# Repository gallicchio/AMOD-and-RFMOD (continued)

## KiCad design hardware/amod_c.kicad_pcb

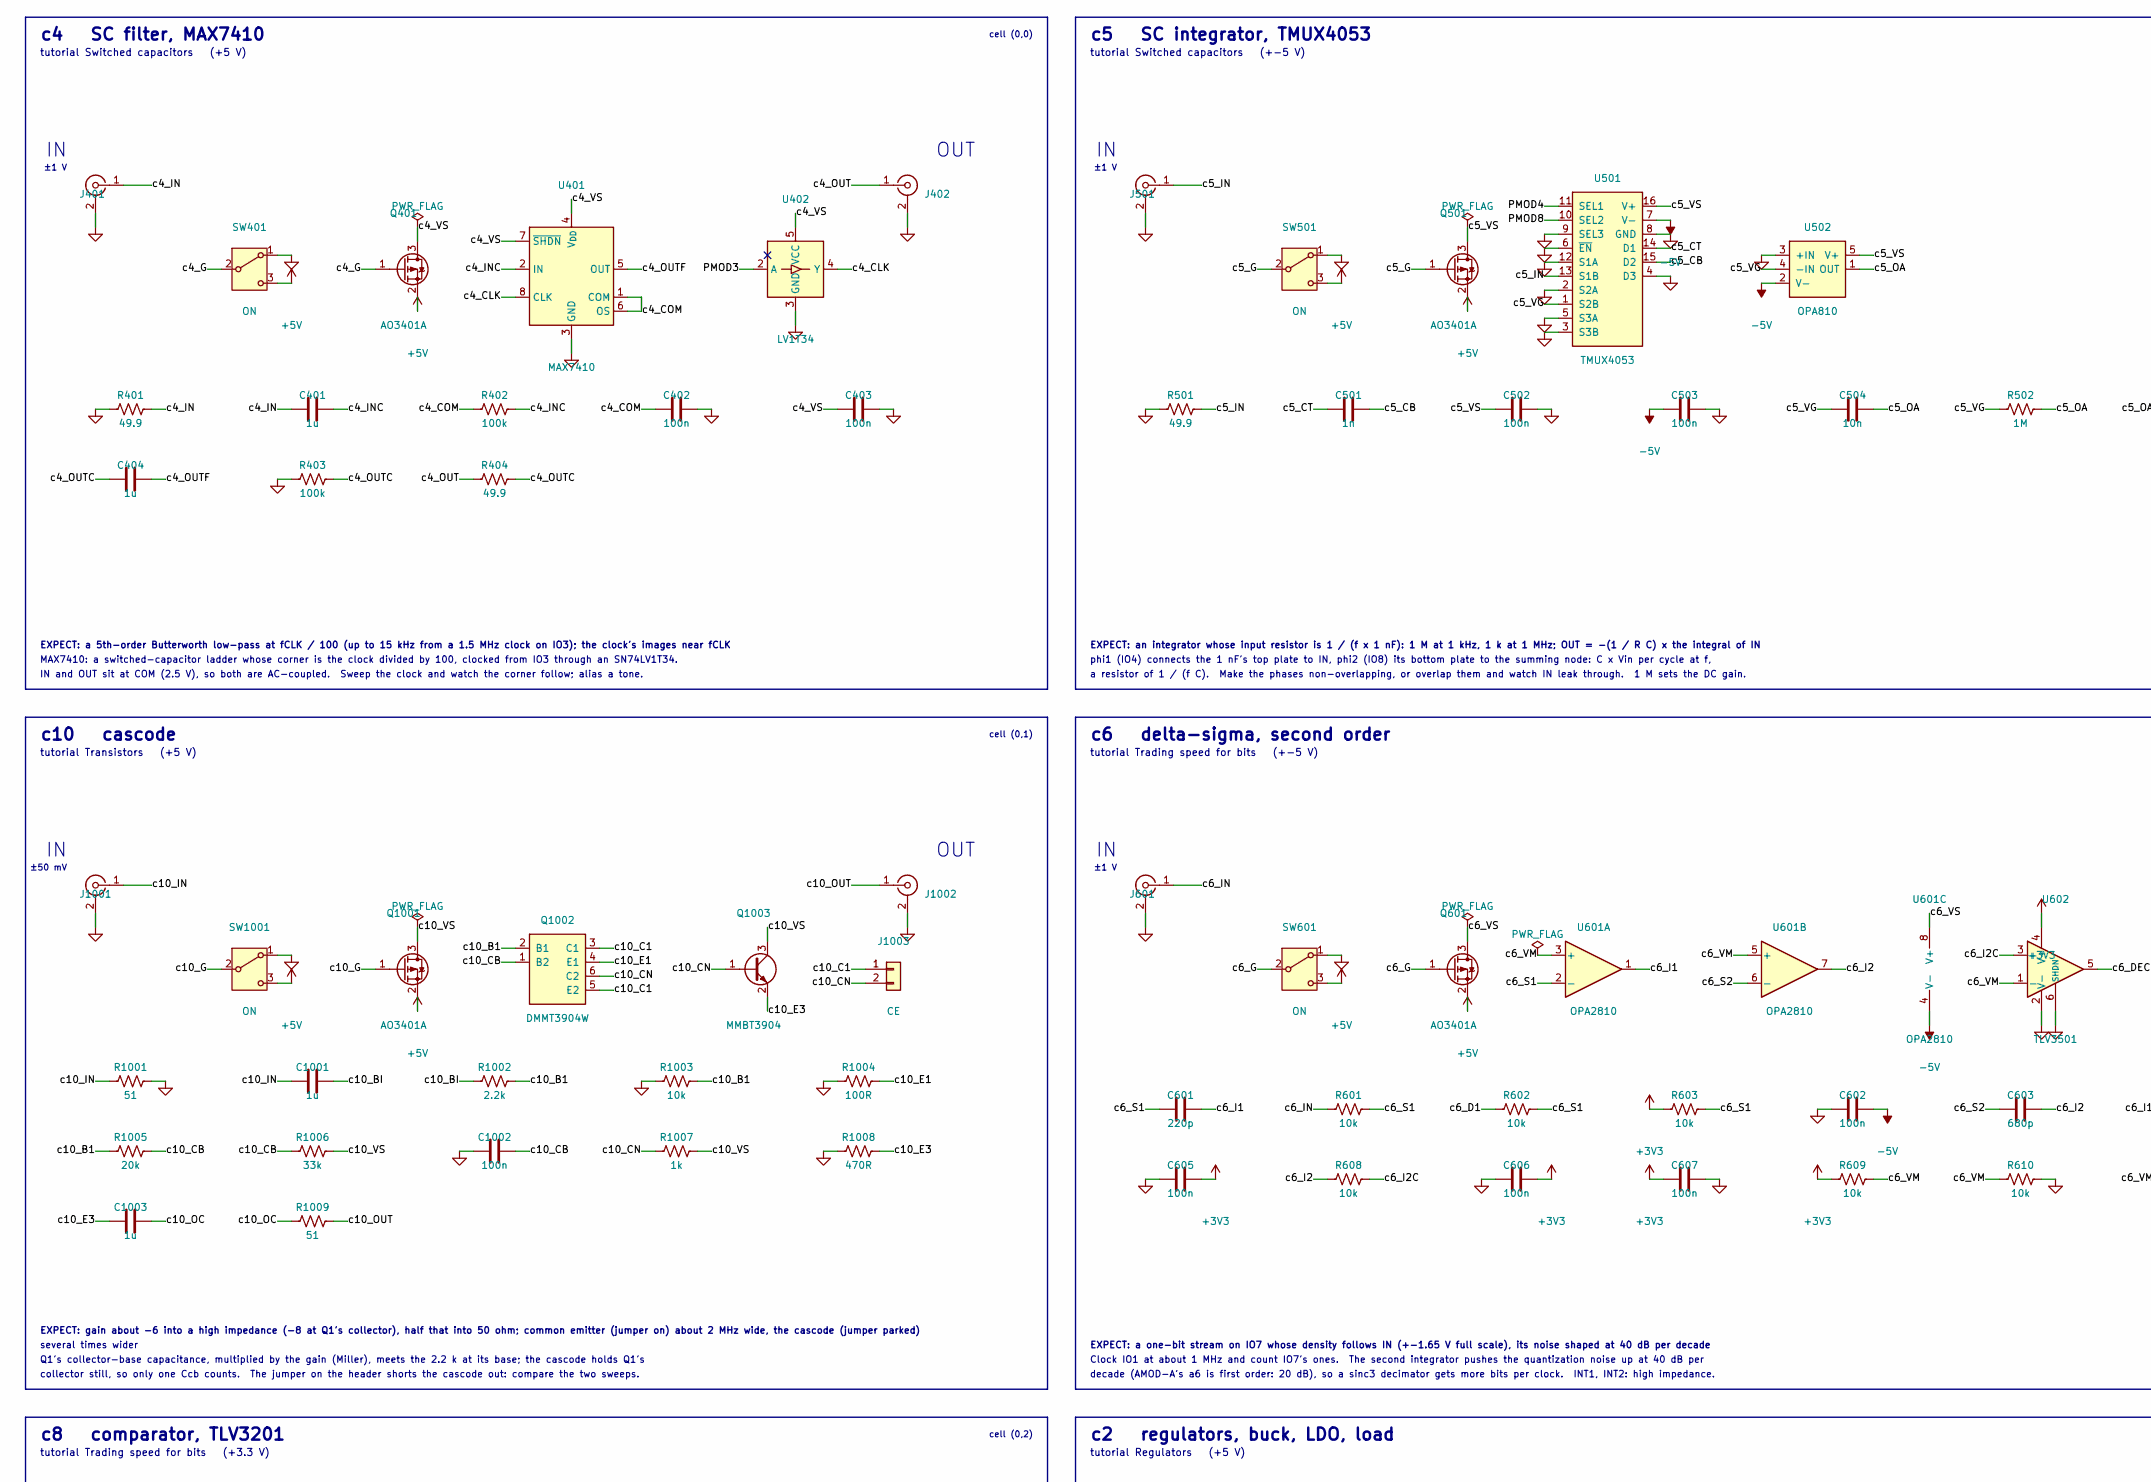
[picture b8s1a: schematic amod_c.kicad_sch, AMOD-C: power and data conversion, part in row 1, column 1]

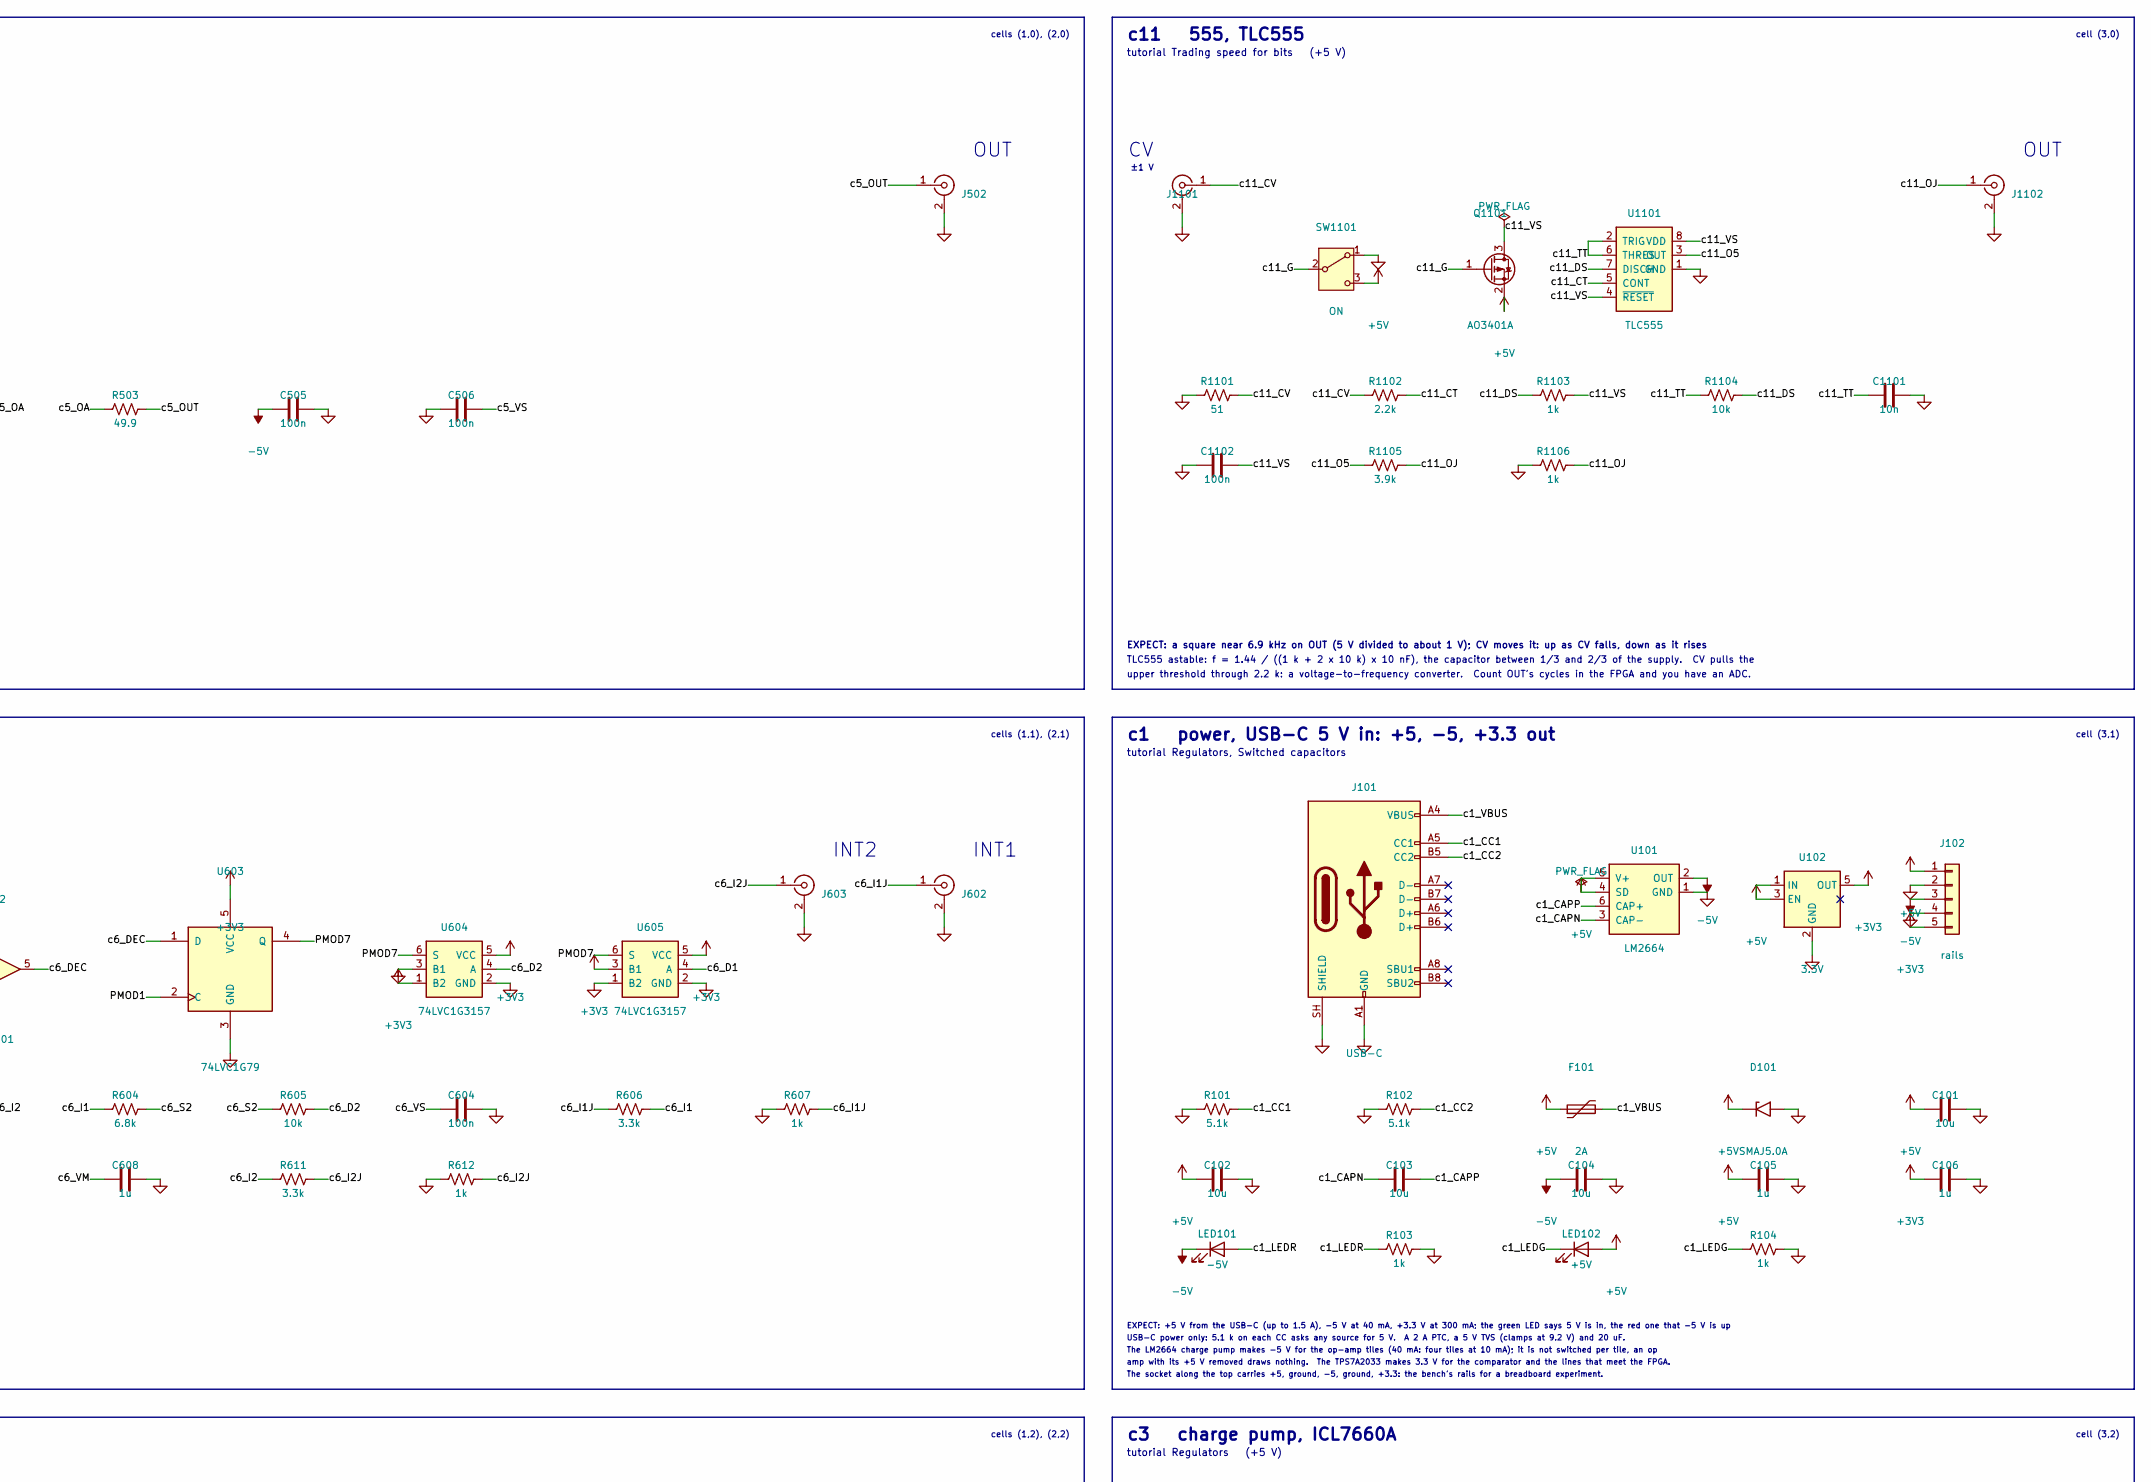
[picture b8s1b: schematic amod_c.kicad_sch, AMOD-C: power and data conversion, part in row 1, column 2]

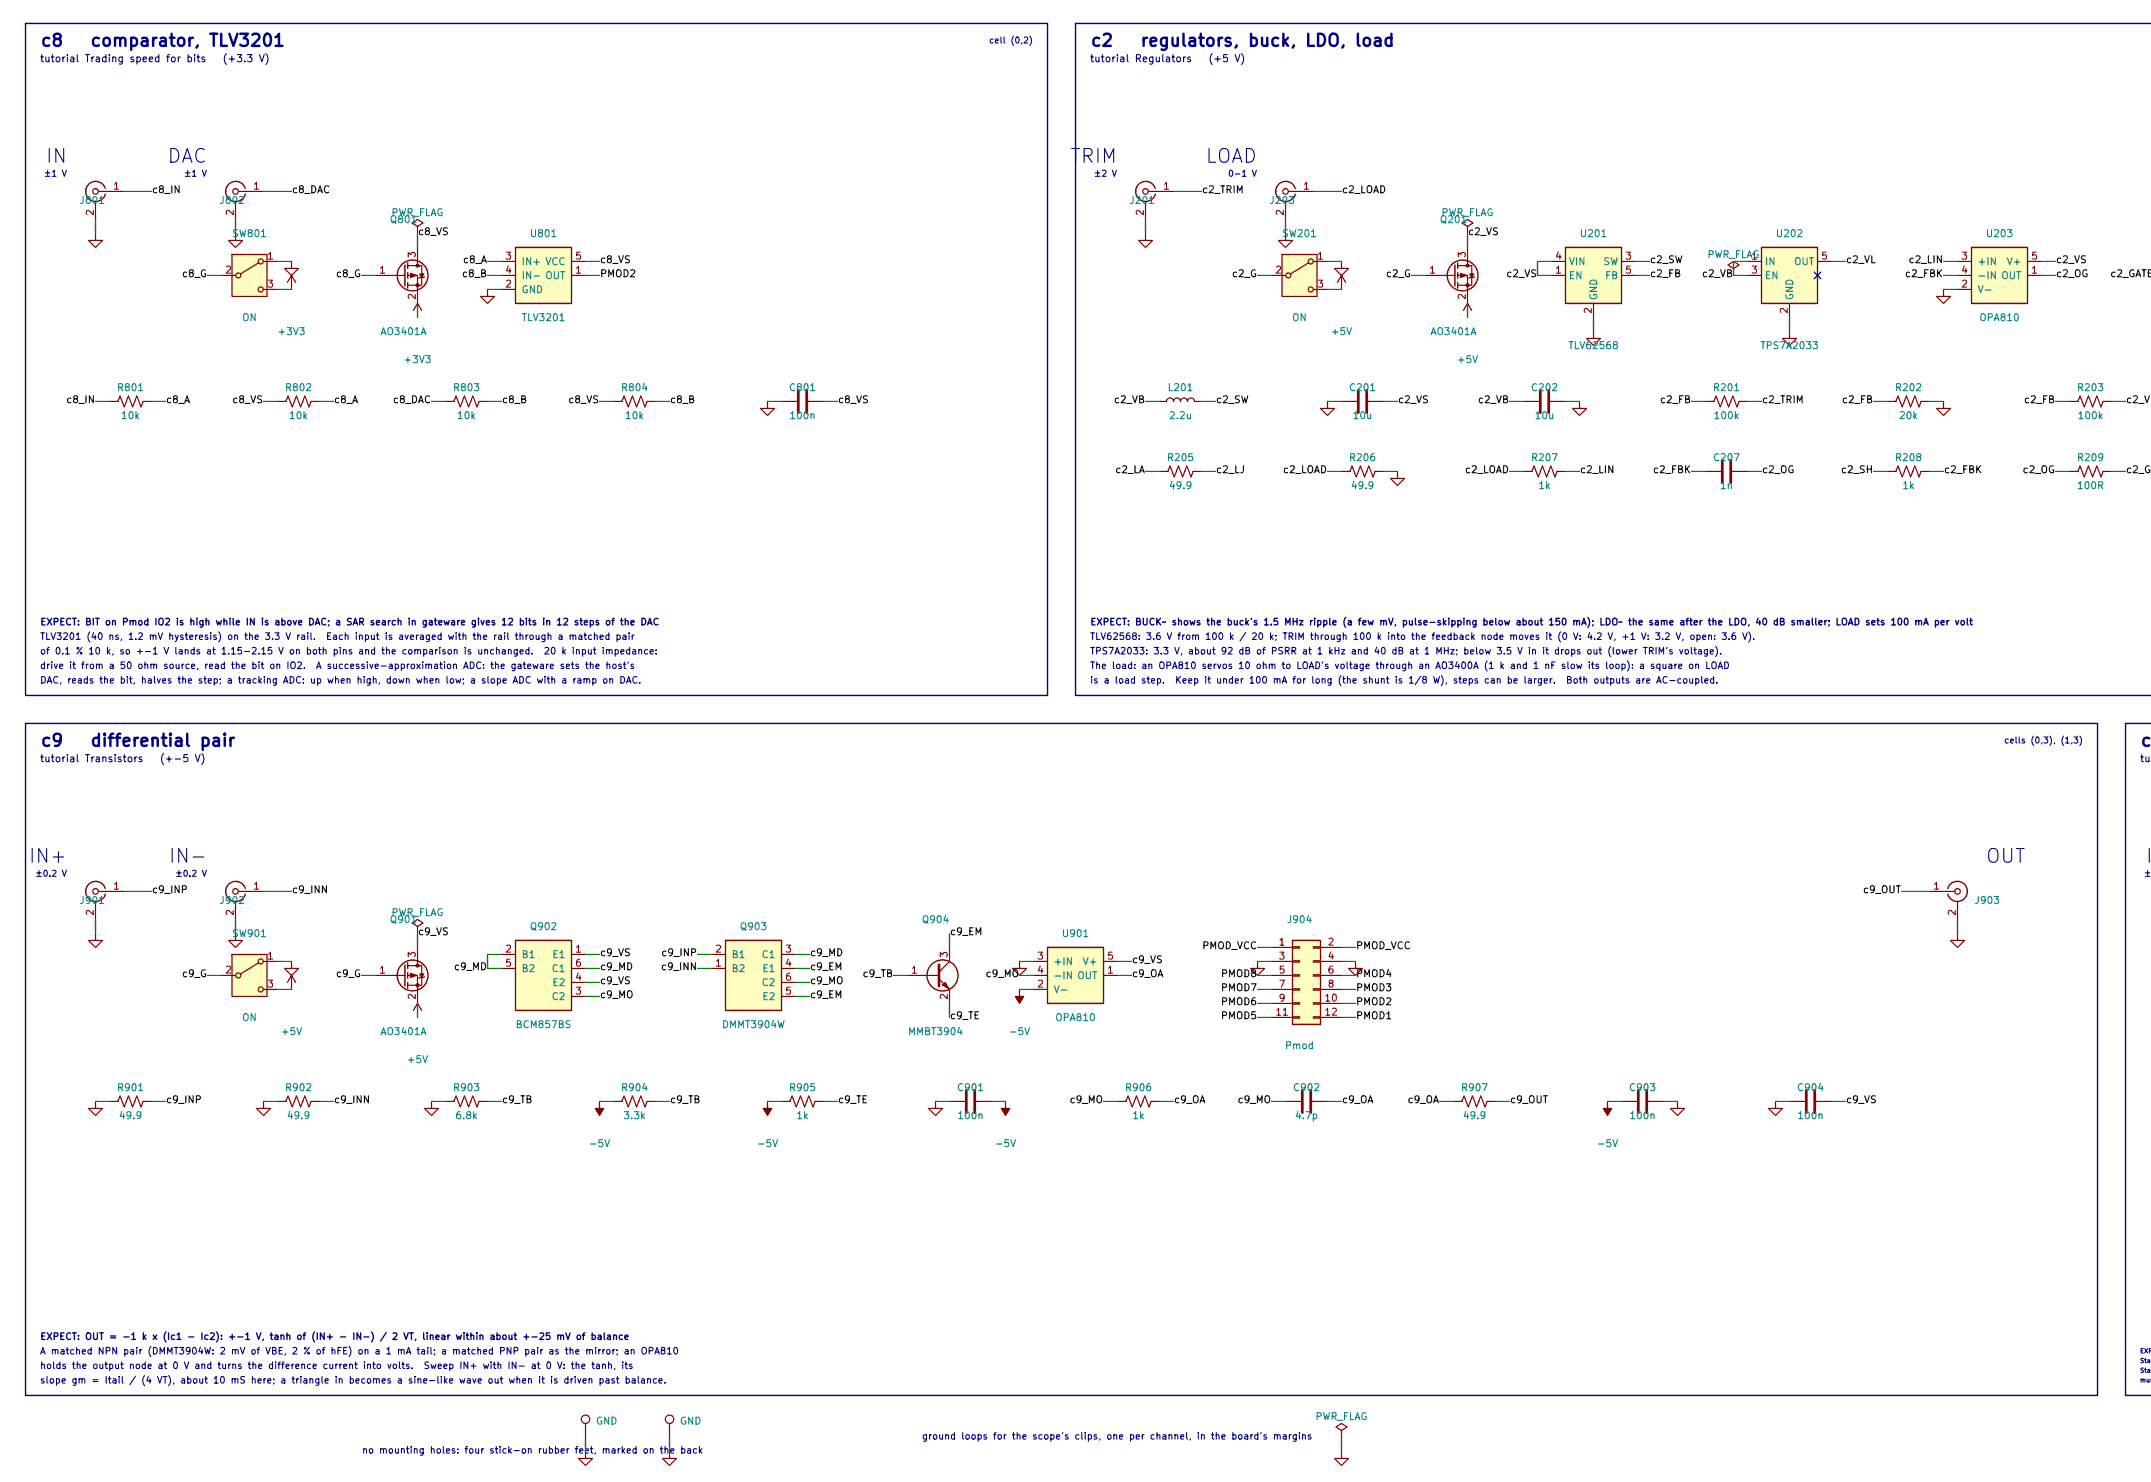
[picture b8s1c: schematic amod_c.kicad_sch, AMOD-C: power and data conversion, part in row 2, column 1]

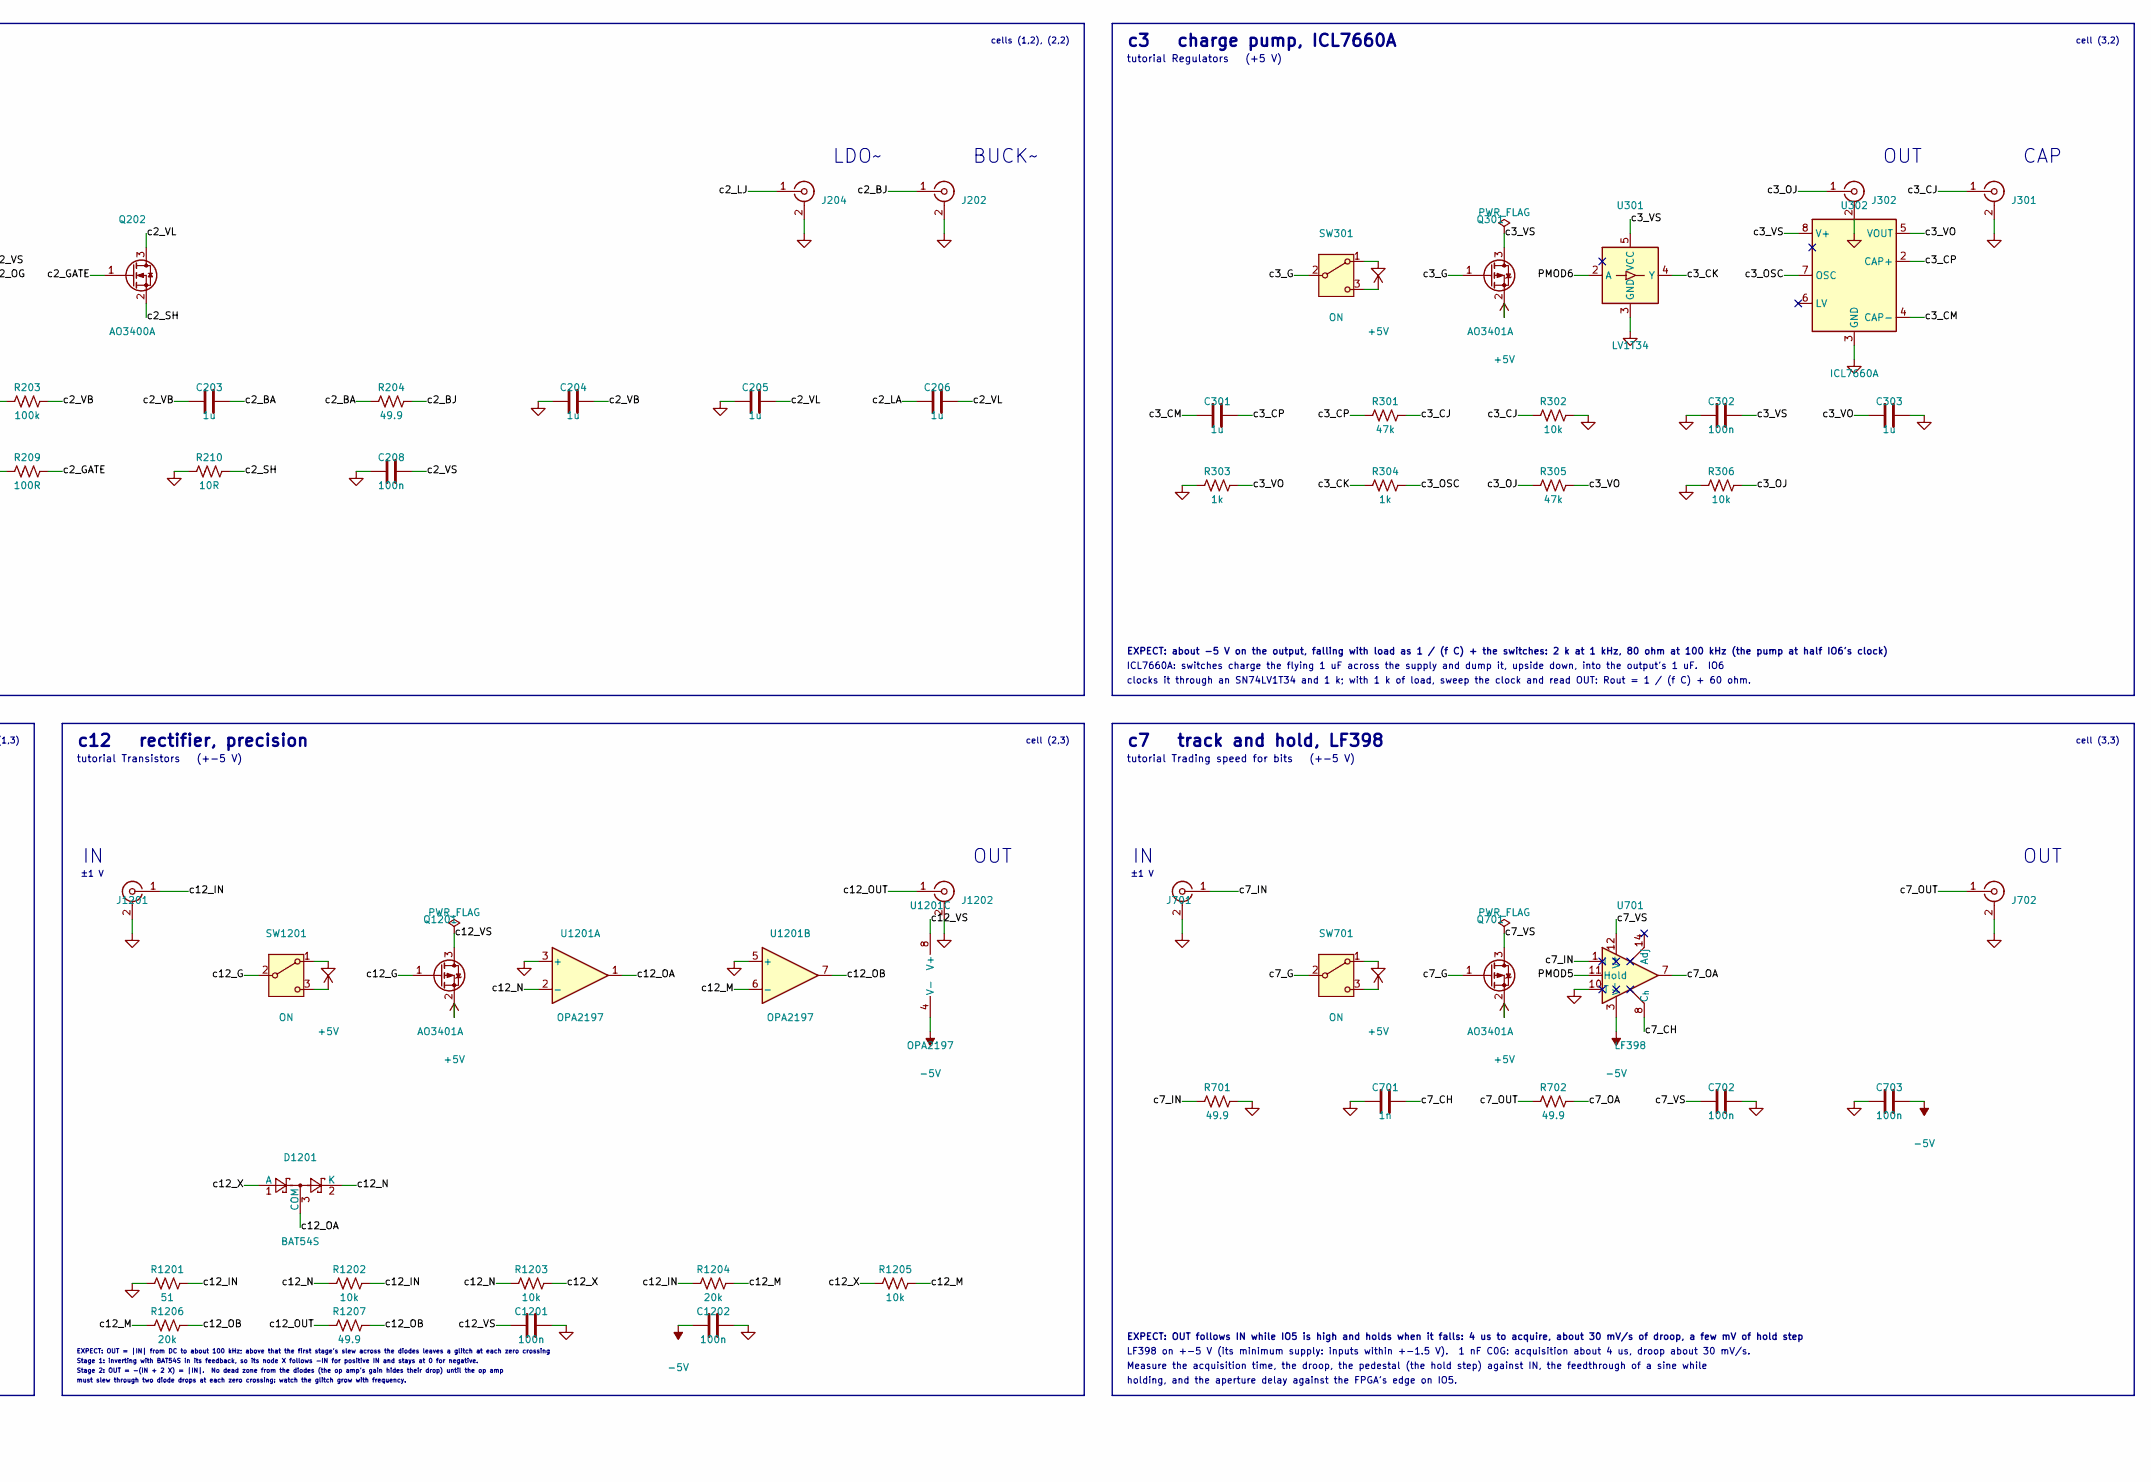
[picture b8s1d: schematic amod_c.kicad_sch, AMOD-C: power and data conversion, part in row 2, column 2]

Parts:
C101, C102, C103, C104, C201, C202: 10u; C_0805_2012Metric; MPN CL21A106KAYNNNE; LCSC C15850
C105, C106: 1u; C_0805_2012Metric; MPN CL21B105KBFNNNE; LCSC C28323
C203, C204, C205, C206, C301, C303, C608: 1u; C_0603_1608Metric; MPN CL10A105KB8NNNC; LCSC C15849
C207, C501, C701: 1n; C_0603_1608Metric; MPN 0603CG102J500NT; LCSC C1636
C208, C302, C402, C403, C502, C503, C505, C506, C602, C604, C605, C606, C607, C702, C703, C901, C903, C904, C1002, C1102, C1201, C1202: 100n; C_0402_1005Metric; MPN CL05B104KO5NNNC; LCSC C1525
C401, C404, C1001, C1003: 1u; C_0402_1005Metric; MPN CL05A105KP5NNNC; LCSC C14445
C504, C1101: 10n; C_0603_1608Metric; MPN GRM1885C1H103JA01D; LCSC C85973
C601: 220p; C_0402_1005Metric; MPN 0402CG221J500NT; LCSC C39122
C603: 680p; C_0402_1005Metric; MPN 0402CG681J500NT; LCSC C301953
C801: 100n; C_0603_1608Metric; MPN CC0603KRX7R9BB104; LCSC C14663
C902: 4.7p; C_0402_1005Metric; MPN 0402CG4R7C500NT; LCSC C1569
D101: SMAJ5.0A; D_SMA; MPN SMAJ5.0A; LCSC C78401
D1201: BAT54S; SOT-23; MPN BAT54S; LCSC C8592
F101: 2A; Fuse_1812_4532Metric; MPN MF-MSMF200-2; LCSC C210837
J101: USB-C; USB_C_Receptacle_HRO_TYPE-C-31-M-12; MPN TYPE-C-31-M-12; LCSC C165948
J102: rails; PinSocket_1x05_P2.54mm_Vertical; MPN PZ254-1-05-Z-8.5; LCSC C2894928
J201, J202, J203, J204, J301, J302, J401, J402, J501, J502, J601, J602, J603, J701, J702, J801, J802, J901, J902, J903, J1001, J1002, J1101, J1102, J1201, J1202: SMA; SMA_BWSMA-KE-Z001_Vertical; MPN BWSMA-KE-Z001; LCSC C496549
J904: Pmod; PinHeader_2x06_P2.54mm_Horizontal_PZ254R-12-12P; MPN PZ254R-12-12P; LCSC C492434
J1003: CE; PinSocket_1x02_P2.54mm_Vertical; MPN PZ254-1-02-Z-8.5; LCSC C2894925
L201: 2.2u; L_Cenker_CKCS201610; MPN WPN201610H2R2MT; LCSC C97005
LED101: -5V; LED_0805_2012Metric_Kbar; MPN NCD0805R1; LCSC C84256
LED102: +5V; LED_0805_2012Metric_Kbar; MPN KT-0805G; LCSC C2297
Q201, Q301, Q401, Q501, Q601, Q701, Q801, Q901, Q1001, Q1101, Q1201: AO3401A; SOT-23; MPN AO3401A; LCSC C15127
Q202: AO3400A; SOT-23; MPN AO3400A; LCSC C20917
Q902: BCM857BS; SOT-363_SC-70-6; MPN BCM857BS-7-F; LCSC C105896
Q903, Q1002: DMMT3904W; SOT-363_SC-70-6; MPN DMMT3904W-7-F; LCSC C155305
Q904, Q1003: MMBT3904; SOT-23; MPN MMBT3904(RANGE:100-300); LCSC C20526
R101, R102: 5.1k; R_0805_2012Metric; MPN 0805W8F5101T5E; LCSC C27834
R103, R104: 1k; R_0805_2012Metric; MPN 0805W8F1001T5E; LCSC C17513
R201, R203, R402, R403: 100k; R_0402_1005Metric; MPN 0402WGF1003TCE; LCSC C25741
R202, R1005, R1204, R1206: 20k; R_0402_1005Metric; MPN 0402WGF2002TCE; LCSC C25765
R204, R503: 49.9; R_0603_1608Metric; MPN SR0603FR-7T49R9L; LCSC C6230117
R205, R206, R401, R404, R501, R701, R702, R901, R902, R907, R1207: 49.9; R_0402_1005Metric; MPN CRCW040249R9FKEDHP; LCSC C844112
R207, R208, R304, R607, R612, R905, R906, R1007, R1103, R1106: 1k; R_0402_1005Metric; MPN 0402WGF1001TCE; LCSC C11702
R209, R1004: 100R; R_0402_1005Metric; MPN 0402WGF1000TCE; LCSC C25076
R210: 10R; R_0805_2012Metric; MPN 0805W8F100JT5E; LCSC C17415
R301, R305: 47k; R_0402_1005Metric; MPN 0402WGF4702TCE; LCSC C25792
R302, R306, R601, R605, R608, R1003, R1104, R1202, R1203, R1205: 10k; R_0402_1005Metric; MPN 0402WGF1002TCE; LCSC C25744
R303: 1k; R_0603_1608Metric; MPN 0603WAF1001T5E; LCSC C21190
R502: 1M; R_0402_1005Metric; MPN 0402WGF1004TCE; LCSC C26083
R602, R603, R609, R610, R801, R802, R803, R804: 10k; R_0603_1608Metric; MPN RT0603BRD0710KL; LCSC C95204
R604, R903: 6.8k; R_0402_1005Metric; MPN RC0402FR-076K8L; LCSC C93940
R606, R611, R904: 3.3k; R_0402_1005Metric; MPN 0402WGF3301TCE; LCSC C25890
R1001, R1009, R1101, R1201: 51; R_0402_1005Metric; MPN 0402WGF510JTCE; LCSC C25125
R1002, R1102: 2.2k; R_0402_1005Metric; MPN 0402WGF2201TCE; LCSC C25879
R1006: 33k; R_0402_1005Metric; MPN 0402WGF3302TCE; LCSC C25779
R1008: 470R; R_0402_1005Metric; MPN 0402WGF4700TCE; LCSC C25117
R1105: 3.9k; R_0402_1005Metric; MPN 0402WGF3901TCE; LCSC C51721
SW201, SW301, SW401, SW501, SW601, SW701, SW801, SW901, SW1001, SW1101, SW1201: ON; SW_SPDT_Shouhan_MSK12C02; MPN MSK12C02; LCSC C431540
TP9901, TP9902: GND; TestPoint_Loop_RH-5019; MPN RH-5019; LCSC C5199800
U101: LM2664; SOT-23-6; MPN LM2664M6X/NOPB; LCSC C108573
U102: 3.3V; SOT-23-5; MPN TPS7A2033PDBVR; LCSC C2862740
U201: TLV62568; SOT-23-5; MPN TLV62568DBVR; LCSC C163219
U202: TPS7A2033; SOT-23-5; MPN TPS7A2033PDBVR; LCSC C2862740
U203, U502, U901: OPA810; SOT-23-5; MPN OPA810IDBVR; LCSC C2833513
U301, U402: LV1T34; SOT-353_SC-70-5; MPN SN74LV1T34DCKR; LCSC C78541
U302: ICL7660A; SOIC-8_3.9x4.9mm_P1.27mm; MPN ICL7660AIBAZA-T; LCSC C7881
U401: MAX7410; MSOP-8_3x3mm_P0.65mm; MPN MAX7410EUA+T; LCSC C17492626
U501: TMUX4053; TSSOP-16_4.4x5mm_P0.65mm; MPN TMUX4053PWR; LCSC C5377936
U601: OPA2810; SOIC-8_3.9x4.9mm_P1.27mm; MPN OPA2810IDR; LCSC C1849413
U602: TLV3501; SOT-23-6; MPN TLV3501AIDBVR; LCSC C193413
U603: 74LVC1G79; SOT-23-5; MPN SN74LVC1G79DBVR; LCSC C42878
U604, U605: 74LVC1G3157; SOT-23-6; MPN SN74LVC1G3157DBVR; LCSC C10426
U701: LF398; SOIC-14_3.9x8.7mm_P1.27mm; MPN LF398MX/NOPB; LCSC C2864267
U801: TLV3201; SOT-353_SC-70-5; MPN TLV3201AQDCKRQ1; LCSC C3658542
U1101: TLC555; SOIC-8_3.9x4.9mm_P1.27mm; MPN TLC555CDR; LCSC C6986
U1201: OPA2197; MSOP-8_3x3mm_P0.65mm; MPN OPA2197IDGKR; LCSC C2867268

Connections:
+3V3: C106.1, C605.2, C606.2, C607.1, J102.5, Q801.2 (S), R603.1, R609.1, SW801.3 (C), U102.5 (OUT), U602.4 (V+), U603.5 (VCC), U604.1 (B2), U604.5 (VCC), U605.3 (B1), U605.5 (VCC)
+5V: C101.1, C102.1, C105.1, D101.1 (A1), F101.1, J102.1, LED102.2 (A), Q201.2 (S), Q301.2 (S), Q401.2 (S), Q501.2 (S), Q601.2 (S), Q701.2 (S), Q901.2 (S), Q1001.2 (S), Q1101.2 (S), Q1201.2 (S), SW201.3 (C), SW301.3 (C), SW401.3 (C), SW501.3 (C), SW601.3 (C), SW701.3 (C), SW901.3 (C), SW1001.3 (C), SW1101.3 (C), SW1201.3 (C), U101.4 (SD), U101.5 (V+), U102.1 (IN), U102.3 (EN)
-5V: C104.1, C503.1, C505.1, C602.2, C703.2, C901.2, C903.1, C1202.1, J102.3, LED101.1 (K), R904.1, R905.1, U101.2 (OUT), U501.7 (V-), U502.2 (V-), U601.4 (V-), U701.3 (V^{-}), U901.2 (V-), U1201.4 (V-)
/PMOD1: J904.12, U603.2 (C)
/PMOD2: J904.10, U801.1 (OUT)
/PMOD3: J904.8, U402.2 (A)
/PMOD4: J904.6, U501.11 (SEL1)
/PMOD5: J904.11, U701.11 (Hold)
/PMOD6: J904.9, U301.2 (A)
/PMOD7: J904.7, U603.4 (Q), U604.6 (S), U605.6 (S)
/PMOD8: J904.5, U501.10 (SEL2)
/PMOD_VCC: J904.1, J904.2
/c1_CAPN: C103.1, U101.3 (CAP-)
/c1_CAPP: C103.2, U101.6 (CAP+)
/c1_CC1: J101.A5 (CC1), R101.2
/c1_CC2: J101.B5 (CC2), R102.2
/c1_LEDG: LED102.1 (K), R104.1
/c1_LEDR: LED101.2 (A), R103.1
/c1_VBUS: F101.2, J101.A4 (VBUS), J101.A9 (VBUS), J101.B4 (VBUS), J101.B9 (VBUS)
/c2_BA: C203.2, R204.1
/c2_BJ: J202.1 (In), R204.2
/c2_FB: R201.1, R202.1, R203.1, U201.5 (FB)
/c2_FBK: C207.1, R208.2, U203.4 (-IN)
/c2_G: Q201.1 (G), SW201.2 (B)
/c2_GATE: Q202.1 (G), R209.2
/c2_LA: C206.1, R205.1
/c2_LIN: R207.2, U203.3 (+IN)
/c2_LJ: J204.1 (In), R205.2
/c2_LOAD: J203.1 (In), R206.1, R207.1
/c2_OG: C207.2, R209.1, U203.1 (OUT)
/c2_SH: Q202.2 (S), R208.1, R210.2
/c2_SW: L201.2, U201.3 (SW)
/c2_TRIM: J201.1 (In), R201.2
/c2_VB: C202.1, C203.1, C204.2, L201.1, R203.2, U202.1 (IN), U202.3 (EN)
/c2_VL: C205.2, C206.2, Q202.3 (D), U202.5 (OUT)
/c2_VS: C201.2, C208.2, Q201.3 (D), U201.1 (EN), U201.4 (VIN), U203.5 (V+)
/c3_CJ: J301.1 (In), R301.2, R302.1
/c3_CK: R304.1, U301.4 (Y)
/c3_CM: C301.1, U302.4 (CAP-)
/c3_CP: C301.2, R301.1, U302.2 (CAP+)
/c3_G: Q301.1 (G), SW301.2 (B)
/c3_OJ: J302.1 (In), R305.1, R306.2
/c3_OSC: R304.2, U302.7 (OSC)
/c3_VO: C303.1, R303.2, R305.2, U302.5 (VOUT)
/c3_VS: C302.2, Q301.3 (D), U301.5 (VCC), U302.8 (V+)
/c4_CLK: U401.8 (CLK), U402.4 (Y)
/c4_COM: C402.1, R402.1, U401.1 (COM), U401.6 (OS)
/c4_G: Q401.1 (G), SW401.2 (B)
/c4_IN: C401.1, J401.1 (In), R401.2
/c4_INC: C401.2, R402.2, U401.2 (IN)
/c4_OUT: J402.1 (In), R404.1
/c4_OUTC: C404.1, R403.2, R404.2
/c4_OUTF: C404.2, U401.5 (OUT)
/c4_VS: C403.1, Q401.3 (D), U401.4 (V_{DD}), U401.7 (~SHDN), U402.5 (VCC)
/c5_CB: C501.2, U501.15 (D2)
/c5_CT: C501.1, U501.14 (D1)
/c5_G: Q501.1 (G), SW501.2 (B)
/c5_IN: J501.1 (In), R501.2, U501.13 (S1B)
/c5_OA: C504.2, R502.2, R503.1, U502.1 (OUT)
/c5_OUT: J502.1 (In), R503.2
/c5_VG: C504.1, R502.1, U501.1 (S2B), U502.4 (-IN)
/c5_VS: C502.1, C506.2, Q501.3 (D), U501.16 (V+), U502.5 (V+)
/c6_D1: R602.1, U605.4 (A)
/c6_D2: R605.2, U604.4 (A)
/c6_DEC: U602.5, U603.1 (D)
/c6_G: Q601.1 (G), SW601.2 (B)
/c6_I1: C601.2, R604.1, R606.2, U601.1
/c6_I1J: J602.1 (In), R606.1, R607.2
/c6_I2: C603.2, R608.1, R611.1, U601.7
/c6_I2C: R608.2, U602.3 (+)
/c6_I2J: J603.1 (In), R611.2, R612.2
/c6_IN: J601.1 (In), R601.1
/c6_S1: C601.1, R601.2, R602.2, R603.2, U601.2 (-)
/c6_S2: C603.1, R604.2, R605.1, U601.6 (-)
/c6_VM: C608.1, R609.2, R610.1, U601.3 (+), U601.5 (+), U602.1 (-)
/c6_VS: C604.1, Q601.3 (D), U601.8 (V+)
/c7_CH: C701.2, U701.8 (C_{h})
/c7_G: Q701.1 (G), SW701.2 (B)
/c7_IN: J701.1 (In), R701.1, U701.1 (I)
/c7_OA: R702.2, U701.7
/c7_OUT: J702.1 (In), R702.1
/c7_VS: C702.1, Q701.3 (D), U701.12 (V^{+})
/c8_A: R801.2, R802.2, U801.3 (IN+)
/c8_B: R803.2, R804.2, U801.4 (IN-)
/c8_DAC: J802.1 (In), R803.1
/c8_G: Q801.1 (G), SW801.2 (B)
/c8_IN: J801.1 (In), R801.1
/c8_VS: C801.2, Q801.3 (D), R802.1, R804.1, U801.5 (VCC)
/c9_EM: Q903.4 (E1), Q903.5 (E2), Q904.3 (C)
/c9_G: Q901.1 (G), SW901.2 (B)
/c9_INN: J902.1 (In), Q903.1 (B2), R902.2
/c9_INP: J901.1 (In), Q903.2 (B1), R901.2
/c9_MD: Q902.2 (B1), Q902.5 (B2), Q902.6 (C1), Q903.3 (C1)
/c9_MO: C902.1, Q902.3 (C2), Q903.6 (C2), R906.1, U901.4 (-IN)
/c9_OA: C902.2, R906.2, R907.1, U901.1 (OUT)
/c9_OUT: J903.1 (In), R907.2
/c9_TB: Q904.1 (B), R903.2, R904.2
/c9_TE: Q904.2 (E), R905.2
/c9_VS: C904.2, Q901.3 (D), Q902.1 (E1), Q902.4 (E2), U901.5 (V+)
/c10_B1: Q1002.2 (B1), R1002.2, R1003.2, R1005.1
/c10_BI: C1001.2, R1002.1
/c10_C1: J1003.1, Q1002.3 (C1), Q1002.5 (E2)
/c10_CB: C1002.2, Q1002.1 (B2), R1005.2, R1006.1
/c10_CN: J1003.2, Q1002.6 (C2), Q1003.1 (B), R1007.1
/c10_E1: Q1002.4 (E1), R1004.2
/c10_E3: C1003.1, Q1003.2 (E), R1008.2
/c10_G: Q1001.1 (G), SW1001.2 (B)
/c10_IN: C1001.1, J1001.1 (In), R1001.1
/c10_OC: C1003.2, R1009.1
/c10_OUT: J1002.1 (In), R1009.2
/c10_VS: Q1001.3 (D), Q1003.3 (C), R1006.2, R1007.2
/c11_CT: R1102.2, U1101.5 (CONT)
/c11_CV: J1101.1 (In), R1101.2, R1102.1
/c11_DS: R1103.1, R1104.2, U1101.7 (DISCH)
/c11_G: Q1101.1 (G), SW1101.2 (B)
/c11_O5: R1105.1, U1101.3 (OUT)
/c11_OJ: J1102.1 (In), R1105.2, R1106.2
/c11_TT: C1101.1, R1104.1, U1101.2 (TRIG), U1101.6 (THRES)
/c11_VS: C1102.2, Q1101.3 (D), R1103.2, U1101.4 (~RESET), U1101.8 (VDD)
/c12_G: Q1201.1 (G), SW1201.2 (B)
/c12_IN: J1201.1 (In), R1201.2, R1202.2, R1204.1
/c12_M: R1204.2, R1205.2, R1206.1, U1201.6 (-)
/c12_N: D1201.2 (K), R1202.1, R1203.1, U1201.2 (-)
/c12_OA: D1201.3 (COM), U1201.1
/c12_OB: R1206.2, R1207.2, U1201.7
/c12_OUT: J1202.1 (In), R1207.1
/c12_VS: C1201.1, Q1201.3 (D), U1201.8 (V+)
/c12_X: D1201.1 (A), R1203.2, R1205.1
GND: C101.2, C102.2, C104.2, C105.2, C106.2, C201.1, C202.2, C204.1, C205.1, C208.1, C302.1, C303.2, C402.2, C403.2, C502.2, C503.2, C505.2, C506.1, C602.1, C604.2, C605.1, C606.1, C607.2, C608.2, C701.1, C702.2, C703.1, C801.1, C901.1, C903.2, C904.1, C1002.1, C1101.2, C1102.1, C1201.2, C1202.2, D101.2 (A2), J101.A1 (GND), J101.A12 (GND), J101.B1 (GND), J101.B12 (GND), J101.SH (SHIELD), J102.2, J102.4, J201.2 (Ext), J202.2 (Ext), J203.2 (Ext), J204.2 (Ext), J301.2 (Ext), J302.2 (Ext), J401.2 (Ext), J402.2 (Ext), J501.2 (Ext), J502.2 (Ext), J601.2 (Ext), J602.2 (Ext), J603.2 (Ext), J701.2 (Ext), J702.2 (Ext), J801.2 (Ext), J802.2 (Ext), J901.2 (Ext), J902.2 (Ext), J903.2 (Ext), J904.3, J904.4, J1001.2 (Ext), J1002.2 (Ext), J1101.2 (Ext), J1102.2 (Ext), J1201.2 (Ext), J1202.2 (Ext), R101.1, R102.1, R103.2, R104.2, R202.2, R206.2, R210.1, R302.2, R303.1, R306.1, R401.1, R403.1, R501.1, R607.1, R610.2, R612.1, R701.2, R901.1, R902.1, R903.1, R1001.2, R1003.1, R1004.1, R1008.1, R1101.1, R1106.1, R1201.1, SW201.1 (A), SW301.1 (A), SW401.1 (A), SW501.1 (A), SW601.1 (A), SW701.1 (A), SW801.1 (A), SW901.1 (A), SW1001.1 (A), SW1101.1 (A), SW1201.1 (A), TP9901.1, TP9902.1, U101.1 (GND), U102.2 (GND), U201.2 (GND), U202.2 (GND), U203.2 (V-), U301.3 (GND), U302.3 (GND), U401.3 (GND), U402.3 (GND), U501.2 (S2A), U501.3 (S3B), U501.4 (D3), U501.5 (S3A), U501.6 (~EN), U501.8 (GND), U501.9 (SEL3), U501.12 (S1A), U502.3 (+IN), U602.2 (V-), U602.6 (SHDN), U603.3 (GND), U604.2 (GND), U604.3 (B1), U605.1 (B2), U605.2 (GND), U701.10 (T), U801.2 (GND), U901.3 (+IN), U1101.1 (GND), U1201.3 (+), U1201.5 (+)

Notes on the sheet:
Stage 1: inverting with BAT54S in its feedback, so its node X follows -IN for positive IN and stays at 0 for negative.
OUT
TPS7A2033: 3.3 V, about 92 dB of PSRR at 1 kHz and 40 dB at 1 MHz; below 3.5 V in it drops out (lower TRIM's voltage).
0-1 V
±1 V
c1 power, USB-C 5 V in: +5, -5, +3.3 out
TLV3201 (40 ns, 1.2 mV hysteresis) on the 3.3 V rail. Each input is averaged with the rail through a matched pair
cell (0,2)
is a load step. Keep it under 100 mA for long (the shunt is 1/8 W), steps can be larger. Both outputs are AC-coupled.
c10 cascode
TRIM
IN and OUT sit at COM (2.5 V), so both are AC-coupled. Sweep the clock and watch the corner follow; alias a tone.
a resistor of 1 / (f C). Make the phases non-overlapping, or overlap them and watch IN leak through. 1 M sets the DC gain.
cell (3,3)
USB-C power only: 5.1 k on each CC asks any source for 5 V. A 2 A PTC, a 5 V TVS (clamps at 9.2 V) and 20 uF.
cells (1,1), (2,1)
DAC
The socket along the top carries +5, ground, -5, ground, +3.3: the bench's rails for a breadboard experiment.
EXPECT: OUT = -1 k x (Ic1 - Ic2): +-1 V, tanh of (IN+ - IN-) / 2 VT, linear within about +-25 mV of balance
The load: an OPA810 servos 10 ohm to LOAD's voltage through an AO3400A (1 k and 1 nF slow its loop): a square on LOAD
±0.2 V
c11 555, TLC555
cell (0,1)
upper threshold through 2.2 k: a voltage-to-frequency converter. Count OUT's cycles in the FPGA and you have an ADC.
DAC, reads the bit, halves the step; a tracking ADC: up when high, down when low; a slope ADC with a ramp on DAC.
Q1's collector-base capacitance, multiplied by the gain (Miller), meets the 2.2 k at its base; the cascode holds Q1's
TLC555 astable: f = 1.44 / ((1 k + 2 x 10 k) x 10 nF), the capacitor between 1/3 and 2/3 of the supply. CV pulls the
of 0.1 % 10 k, so +-1 V lands at 1.15-2.15 V on both pins and the comparison is unchanged. 20 k input impedance:
tutorial Trading speed for bits (+5 V)
ICL7660A: switches charge the flying 1 uF across the supply and dump it, upside down, into the output's 1 uF. IO6
amp with its +5 V removed draws nothing. The TPS7A2033 makes 3.3 V for the comparator and the lines that meet the FPGA.
tutorial Switched capacitors (+-5 V)
holding, and the aperture delay against the FPGA's edge on IO5.
c3 charge pump, ICL7660A
EXPECT: a square near 6.9 kHz on OUT (5 V divided to about 1 V); CV moves it: up as CV falls, down as it rises
The LM2664 charge pump makes -5 V for the op-amp tiles (40 mA: four tiles at 10 mA); it is not switched per tile, an op
c8 comparator, TLV3201
MAX7410: a switched-capacitor ladder whose corner is the clock divided by 100, clocked from IO3 through an SN74LV1T34.
several times wider
cell (2,3)
